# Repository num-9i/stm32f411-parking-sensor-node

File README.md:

# STM32F411RE Parking Sensor Node

STM32F411RE 기반으로 초음파 거리 측정, 주차 상태 판정, RGB LED 표시, Modbus RTU/RS485 통신을 구현한 주차 센서 노드 프로젝트입니다.

HC-SR04의 Echo pulse를 Timer Input Capture로 비동기 측정하고, 측정 결과에 hysteresis와 entry/exit delay를 적용해 `FREE / OCCUPIED / ERROR` 상태를 판정합니다.

센서 상태와 설정값은 Modbus Holding Register에 매핑했으며, `0x03 Read Holding Registers`와 `0x06 Write Single Register`를 통해 외부 Modbus Master에서 조회 및 변경할 수 있도록 구현했습니다.

현재 브레드보드 환경에서 펌웨어와 RS485 통신 검증을 완료했으며, NUCLEO-F411RE용 Carrier PCB도 Gerber/Drill 파일 생성 단계까지 완료했습니다. 실제 PCB 제작과 Bring-up은 다음 단계로 진행할 예정입니다.

## Project Status

- [x] Pin Map 정의
- [x] HC-SR04 거리 측정
- [x] TIM2 Input Capture / Interrupt 처리
- [x] 거리 측정 Timeout / Error Counter
- [x] FREE / OCCUPIED / ERROR 상태 판정
- [x] Hysteresis / Entry Delay / Exit Delay
- [x] RGB LED 상태 표시
- [x] Modbus RTU Function `0x03`
- [x] Modbus RTU Function `0x06`
- [x] Runtime Configuration
- [x] Modbus Exception Response
- [x] RS485 실통신 검증
- [x] Carrier PCB Schematic
- [x] Carrier PCB Layout / Routing
- [x] Carrier PCB ERC / DRC Verification
- [x] Gerber / Drill File Generation & Inspection
- [x] MAX3485용 PB5 DE/RE 제어 펌웨어 반영
- [ ] UART CLI
- [ ] PCB Fabrication
- [ ] PCB Bring-up / Hardware Verification

## System Overview

전체 데이터 흐름은 다음과 같습니다.

```text
HC-SR04
   │
   │ Echo Pulse
   ↓
TIM2 Input Capture
   │
   ↓
Distance Measurement
   │
   ↓
Parking State Logic
FREE / OCCUPIED / ERROR
   │
   ├──────────────→ RGB LED
   │
   ↓
Modbus Register Layer
   │
   ↓
Modbus RTU
   │
   ↓
USART1 / RS485
   │
   ↓
External Modbus Master
```

HC-SR04의 Echo pulse는 `TIM2_CH1 Input Capture`로 측정합니다.

측정된 거리 값은 주차 상태 판정 로직으로 전달되며, hysteresis와 entry/exit delay를 적용해 순간적인 거리 변화로 상태가 불필요하게 전환되는 것을 줄였습니다.

판정 결과와 센서 상태, 오류 카운터, 설정값은 Modbus Holding Register에 매핑해 외부 Master에서 확인할 수 있도록 구성했습니다.

## Hardware

### MCU / Development Board

- MCU: STM32F411RET6
- Board: NUCLEO-F411RE
- System Clock: 84 MHz

### Sensor / Indicator

- Distance Sensor: HC-SR04
- Status Indicator: Common Cathode RGB LED
- HC-SR04 Echo Interface: 1 kΩ / 2 kΩ Voltage Divider

### Communication

- Modbus UART: USART1
- Debug UART: USART2 / ST-LINK VCP
- Protocol: Modbus RTU
- Prototype RS485: Auto-direction TTL-to-RS485 Module
- Carrier PCB RS485: MAX3485
- PC Interface: USB-to-RS485 Adapter

상세 핀 구성은 아래 문서를 참고합니다.

- [Pin Map](docs/pin_map.md)

## HC-SR04 Distance Measurement

HC-SR04의 Trigger 신호를 출력한 뒤 Echo pulse의 High 구간을 측정해 거리를 계산합니다.

Echo 입력은 `PA0 / TIM2_CH1`에 연결하고, Timer를 1 MHz로 설정해 1 us 단위로 pulse width를 측정합니다.

```text
IDLE
  ↓
Trigger Pulse
  ↓
WAIT_RISING
  ↓
Rising Edge Capture
  ↓
WAIT_FALLING
  ↓
Falling Edge Capture
  ↓
Pulse Width Calculation
  ↓
DATA_READY
```

거리 계산에는 다음 관계를 사용합니다.

```text
Distance_mm = PulseWidth_us × 343 / 2000
```

센서 측정 범위는 약 `20 ~ 4000 mm`로 제한하며, 범위를 벗어난 pulse는 Invalid Pulse로 처리합니다.

정상적인 Echo 신호가 들어오지 않을 경우 무한 대기하지 않도록 Timeout을 적용했습니다.

구분하는 오류 항목은 다음과 같습니다.

- Rising Edge Timeout
- Falling Edge Timeout
- Invalid Pulse

각 오류는 별도의 Counter로 기록해 Modbus를 통해 확인할 수 있습니다.

## Parking State Logic

주차 상태는 다음 세 가지로 구분합니다.

| Value | State | Description |
|---:|---|---|
| `0` | FREE | 주차 공간이 비어 있는 상태 |
| `1` | OCCUPIED | 차량이 감지된 상태 |
| `2` | ERROR | 거리 측정이 일정 시간 이상 유효하지 않은 상태 |

기본 설정값은 다음과 같습니다.

```text
Occupied Threshold = 500 mm
Hysteresis         = 50 mm
Entry Delay        = 500 ms
Exit Delay         = 1000 ms
```

FREE 상태에서 거리가 `Occupied Threshold` 이하로 Entry Delay 동안 유지되면 OCCUPIED로 전환됩니다.

OCCUPIED 상태에서는 다음 기준을 사용합니다.

```text
Free Threshold =
    Occupied Threshold + Hysteresis
```

기본값 기준으로:

```text
Occupied Threshold = 500 mm
Free Threshold     = 550 mm
```

이므로 `500 mm < distance <= 550 mm` 구간에서는 현재 상태를 유지합니다.

따라서 임계값 부근에서 측정값이 흔들려도 상태가 즉시 반복 전환되지 않습니다.

거리 측정이 일정 시간 이상 유효하지 않을 경우 ERROR 상태로 전환합니다.

## RGB LED

주차 상태는 RGB LED로 표시합니다.

| Parking State | LED |
|---|---|
| FREE | Green |
| OCCUPIED | Red |
| ERROR | Blue |

GPIO 구성:

```text
PB12 → Red
PB13 → Green
PB14 → Blue
```

RGB LED는 Active High 방식으로 제어합니다.

## Modbus RTU / RS485

외부 장치에서 센서 상태와 설정값을 확인하거나 변경할 수 있도록 Modbus RTU Slave를 구현했습니다.

지원하는 Function Code는 다음과 같습니다.

- `0x03` Read Holding Registers
- `0x06` Write Single Register

통신 설정:

- Slave ID: `1`
- Baud Rate: `115200`
- Format: `8-N-1`
- Interface: USART1 / RS485

### Prototype RS485

브레드보드 프로토타입에서는 자동 방향 제어 TTL-to-RS485 모듈을 사용했습니다.

```text
PA9  / USART1_TX  → RS485 Module RXD
PA10 / USART1_RX  ← RS485 Module TXD
```

모듈 내부에서 송수신 방향을 자동으로 전환하므로 별도의 DE/RE GPIO가 필요하지 않습니다.

### Carrier PCB RS485

Carrier PCB에서는 `MAX3485`를 사용합니다.

```text
PA9  / USART1_TX  → MAX3485 DI
PA10 / USART1_RX  ← MAX3485 RO
PB5               → MAX3485 DE + /RE
```

`DE`와 `/RE`는 하나의 GPIO로 묶어 다음과 같이 제어합니다.

```text
PB5 LOW  → Receive Mode
PB5 HIGH → Transmit Mode
```

Modbus 응답을 송신하기 직전에 PB5를 HIGH로 설정하고, `HAL_UART_Transmit()` 완료 후 LOW로 복귀시켜 다시 Receive Mode로 전환합니다.

PCB에는 PB5에 10 kΩ Pull-down 저항을 적용해 MCU Reset 중에도 기본적으로 Driver가 비활성화되고 Receiver가 활성화되도록 구성했습니다.

브레드보드의 자동 방향 제어 모듈에는 PB5가 연결되지 않으므로, 해당 제어 코드를 추가한 뒤에도 기존 Prototype의 FC03 / FC06 통신이 정상적으로 동작하는 것을 확인했습니다.

## Holding Register Map

| Address | Name | Access |
|---|---|---|
| `0x0000` | Distance_mm | R |
| `0x0001` | Parking_State | R |
| `0x0002` | Status_Flags | R |
| `0x0003` | Total_Error_Count | R |
| `0x0004` | Rising_Timeout_Count | R |
| `0x0005` | Falling_Timeout_Count | R |
| `0x0006` | Invalid_Pulse_Count | R |
| `0x0007` | Occupied_Threshold_mm | R/W |
| `0x0008` | Hysteresis_mm | R/W |
| `0x0009` | Entry_Delay_ms | R/W |
| `0x000A` | Exit_Delay_ms | R/W |

상세한 Register Map과 설정값 검증 규칙은 아래 문서에 정리했습니다.

- [Modbus Register Map](docs/register_map.md)

## Runtime Configuration

`0x0007`~`0x000A` Register는 Modbus `0x06 Write Single Register`를 통해 실행 중에 변경할 수 있습니다.

예를 들어 Occupied Threshold의 기본값은 500 mm입니다.

```text
Register: 0x0007

500 mm
0x01F4

      ↓ FC06

300 mm
0x012C
```

설정값을 변경하면 주차 상태 판정 로직에서 즉시 새로운 값을 사용합니다.

현재 설정값은 RAM에만 저장되므로 Reset 또는 전원 재인가 후에는 기본값으로 돌아갑니다.

## Modbus Exception Handling

지원하지 않는 요청이나 잘못된 설정값에는 Modbus Exception Response를 반환합니다.

| Exception | Description |
|---|---|
| `0x01` | Illegal Function |
| `0x02` | Illegal Data Address |
| `0x03` | Illegal Data Value |

예를 들어 읽기 전용 Register인 `0x0000`에 `0x06` Write 요청을 보내면 `0x02 Illegal Data Address`를 반환합니다.

허용 범위를 벗어난 Occupied Threshold를 설정하면 `0x03 Illegal Data Value`를 반환합니다.

## Verification

### FC03 — Holding Register Read

Modbus Client에서 `0x0000`~`0x000A` Register를 한 번에 읽어 거리, 주차 상태, 오류 카운터, 설정값을 확인했습니다.

### Request / Response Frame

UART Debug 출력을 통해 실제 Modbus RTU Request와 Response 데이터를 확인했습니다.

### FC06 — Runtime Threshold Change

Occupied Threshold를 `500 mm`에서 `300 mm`로 변경한 뒤 Write 결과와 실제 주차 상태 전환 기준 변경을 확인했습니다.

### Exception — Illegal Data Address

읽기 전용 Register에 Write 요청을 전송해 `0x02 Illegal Data Address` 응답을 확인했습니다.

### Exception — Illegal Data Value

허용 범위를 벗어난 설정값을 전송해 `0x03 Illegal Data Value` 응답을 확인했습니다.

## Carrier PCB Design

브레드보드 프로토타입을 실제 조립 가능한 구조로 확장하기 위해 NUCLEO-F411RE용 Carrier PCB를 KiCad로 설계했습니다.

Carrier PCB에는 다음 회로를 포함합니다.

- NUCLEO-F411RE Interface
- HC-SR04 Connector
- HC-SR04 Echo Voltage Divider
- RGB Status LED
- MAX3485 RS485 Transceiver
- MAX3485 100 nF Decoupling Capacitor
- PB5 DE/RE Pull-down
- RS485 A / B / GND Terminal Block
- Selectable 120 Ω RS485 Termination

RS485 종단저항은 Solder Jumper를 사용해 필요할 때만 활성화할 수 있도록 구성했습니다.

```text
RS485_A ── 120 Ω ── JP1 ── RS485_B
```

### PCB 3D Overview

### RS485 / Sensor Section

PCB는 2-Layer로 구성했으며, B.Cu에 GND Copper Zone을 적용했습니다. ERC와 DRC는 모두 Error / Warning 0건을 확인했습니다.

구매한 Common Cathode RGB LED의 `B-G-K-R` Pin Order에 맞춰 전용 Footprint를 추가하고, D1의 Drill Diameter를 `0.8 mm`로 조정해 Annular Ring 규칙을 만족시켰습니다.

이후 Gerber와 PTH / NPTH Drill File을 생성하고 KiCad Gerber Viewer에서 Edge.Cuts, Copper, Solder Mask, Silkscreen, Drill Layer를 확인했습니다.

KiCad 프로젝트와 제조용 출력 파일은 다음 경로에 포함되어 있습니다.

```text
hardware/
└─ parking_sensor_node/
   ├─ parking_sensor_node.kicad_pro
   ├─ parking_sensor_node.kicad_sch
   ├─ parking_sensor_node.kicad_pcb
   ├─ fp-lib-table
   ├─ footprints/
   │  └─ ParkingSensor.pretty/
   │     └─ LED_D5.0mm-4_RGB_BGKR.kicad_mod
   └─ gerber/
      ├─ *.gbr
      ├─ *-PTH.drl
      └─ *-NPTH.drl
```

## Software Structure

주요 모듈은 다음과 같이 분리했습니다.

```text
Core/
├─ Inc/
│  ├─ hcsr04.h
│  ├─ parking_logic.h
│  ├─ rgb_led.h
│  ├─ app_config.h
│  ├─ modbus_crc.h
│  ├─ modbus_registers.h
│  └─ modbus_rtu.h
│
└─ Src/
   ├─ hcsr04.c
   ├─ parking_logic.c
   ├─ rgb_led.c
   ├─ app_config.c
   ├─ modbus_crc.c
   ├─ modbus_registers.c
   └─ modbus_rtu.c
```

각 모듈의 역할을 분리해 센서 측정, 상태 판정, 설정값 관리, Register Mapping, Modbus Frame 처리가 서로 직접 의존하지 않도록 구성했습니다.

## Current Limitations

현재 구현은 프로젝트 범위에 맞춰 다음과 같이 제한되어 있습니다.

- Modbus Function `0x03`, `0x06`만 지원
- UART RX는 현재 지원하는 8-byte Request Frame을 기준으로 처리
- Generic Modbus RTU Frame Gap Detection 미구현
- 통신 중 Partial Frame이 남은 상태에서 Master가 재연결될 경우 Frame 정렬이 깨질 수 있음
- 설정값은 RAM에만 저장
- UART CLI 미구현
- Carrier PCB 실물 제작 및 Bring-up 미완료
- MAX3485 기반 수동 DE/RE 제어는 펌웨어에 반영했으나 실제 Carrier PCB에서의 Hardware Verification은 아직 진행 전

현재 브레드보드 환경에서는 센서 측정, 상태 판정, RGB 표시, Modbus FC03 / FC06, Exception Response 및 RS485 실통신까지 검증했습니다.

## Next Step

다음 단계에서는 구매한 부품이 도착한 뒤 실제 부품과 Footprint를 대조하고 Carrier PCB 제작 및 Bring-up을 진행합니다.

제작 전 실물 기준으로 다음 항목을 확인할 예정입니다.

- MAX3485 SOIC-8 Package
- 3-pin RS485 Terminal Block의 5.08 mm Pitch / 방향
- RGB LED의 실제 Pin Order / Lead Pitch
- HC-SR04 Connector 및 기구 간섭

PCB 제작 후에는 다음 항목을 검증할 예정입니다.

```text
Power / Ground
    ↓
HC-SR04 Measurement
    ↓
RGB State Output
    ↓
MAX3485 DE/RE Control
    ↓
Modbus FC03 / FC06
    ↓
Exception Response
    ↓
Long-term Communication Test
```

PCB 제작 후에는 브레드보드에서 검증한 기능을 Carrier PCB에서도 동일한 순서로 Bring-up할 예정입니다.

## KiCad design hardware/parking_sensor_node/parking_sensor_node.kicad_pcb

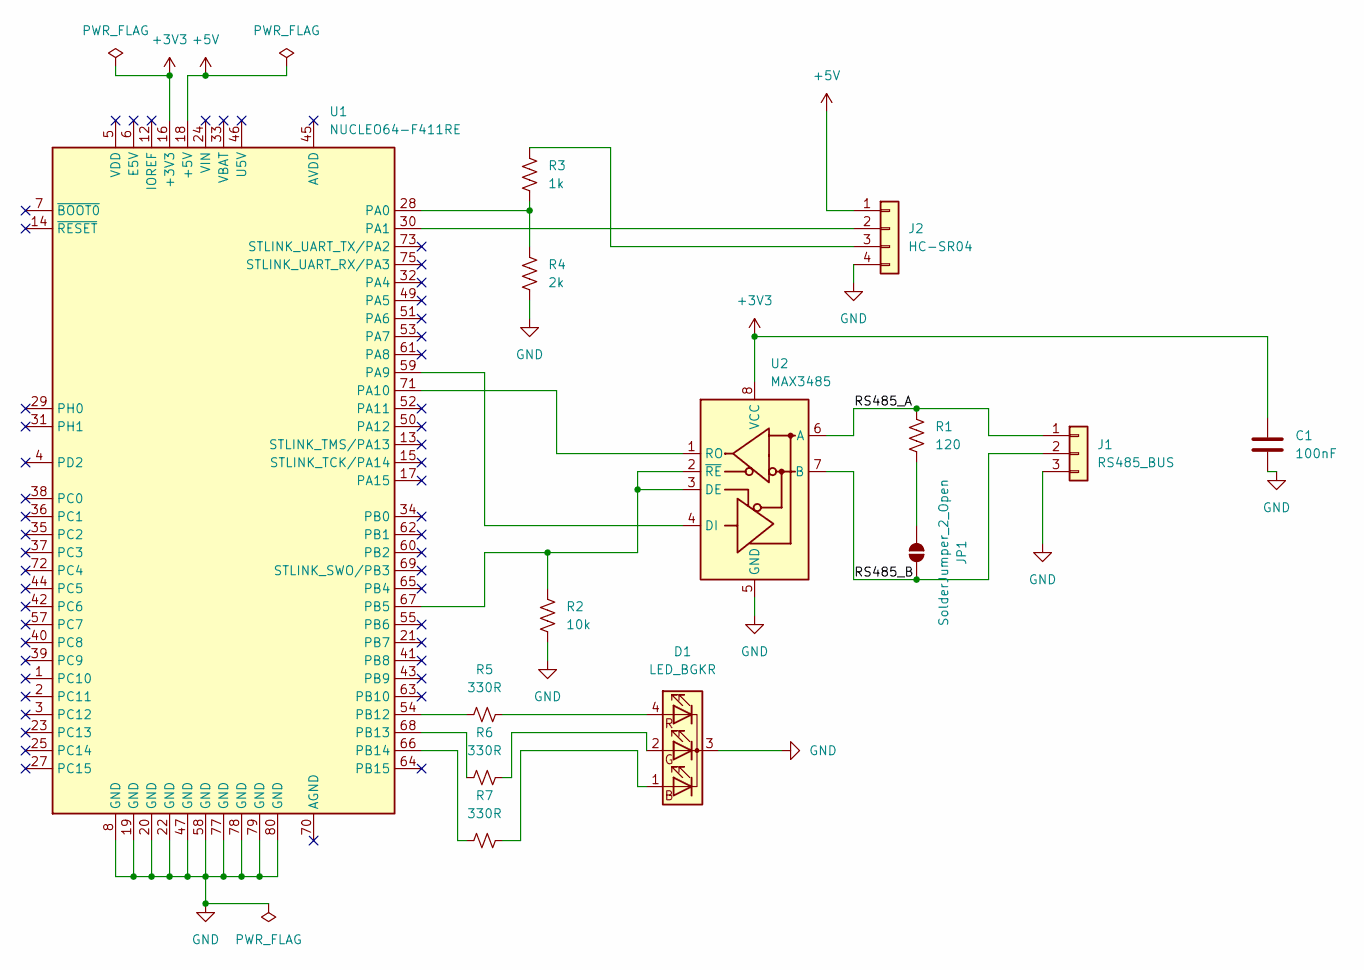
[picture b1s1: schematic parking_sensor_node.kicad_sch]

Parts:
C1: 100nF; C_0805_2012Metric
D1: LED_BGKR; LED_D5.0mm-4_RGB_BGKR
J1: RS485_BUS; TerminalBlock_Phoenix_MKDS-3-3-5.08_1x03_P5.08mm_Horizontal
J2: HC-SR04; PinSocket_1x04_P2.54mm_Vertical
JP1: SolderJumper_2_Open; SolderJumper-2_P1.3mm_Open_Pad1.0x1.5mm
R1: 120; R_0805_2012Metric
R2: 10k; R_0805_2012Metric
R3: 1k; R_0805_2012Metric
R4: 2k; R_0805_2012Metric
R5, R6, R7: 330R; R_0805_2012Metric
U1: NUCLEO64-F411RE; ST_Morpho_Connector_64_STLink
U2: MAX3485; SOIC-8_3.9x4.9mm_P1.27mm

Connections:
+3V3: C1.1, U1.16 (+3V3), U2.8 (VCC)
+5V: J2.1, U1.18 (+5V)
/RS485_A: J1.1, R1.1, U2.6 (A)
/RS485_B: J1.2, JP1.2 (B), U2.7 (B)
GND: C1.2, D1.3 (K), J1.3, J2.4, R2.2, R4.2, U1.8 (GND), U1.19 (GND), U1.20 (GND), U1.22 (GND), U1.47 (GND), U1.58 (GND), U1.77 (GND), U1.78 (GND), U1.79 (GND), U1.80 (GND), U2.5 (GND)
unnamed: D1.1 (BA), R7.2
unnamed: D1.2 (GA), R6.2
unnamed: D1.4 (RA), R5.2
unnamed: J2.2, U1.30 (PA1)
unnamed: J2.3, R3.1
unnamed: JP1.1 (A), R1.2
unnamed: R3.2, R4.1, U1.28 (PA0)
unnamed: U1.59 (PA9), U2.4 (DI)
unnamed: U1.71 (PA10), U2.1 (RO)
unnamed: R2.1, U1.67 (PB5), U2.2 (~RE), U2.3 (DE)
unnamed: R5.1, U1.54 (PB12)
unnamed: R6.1, U1.68 (PB13)
unnamed: R7.1, U1.66 (PB14)

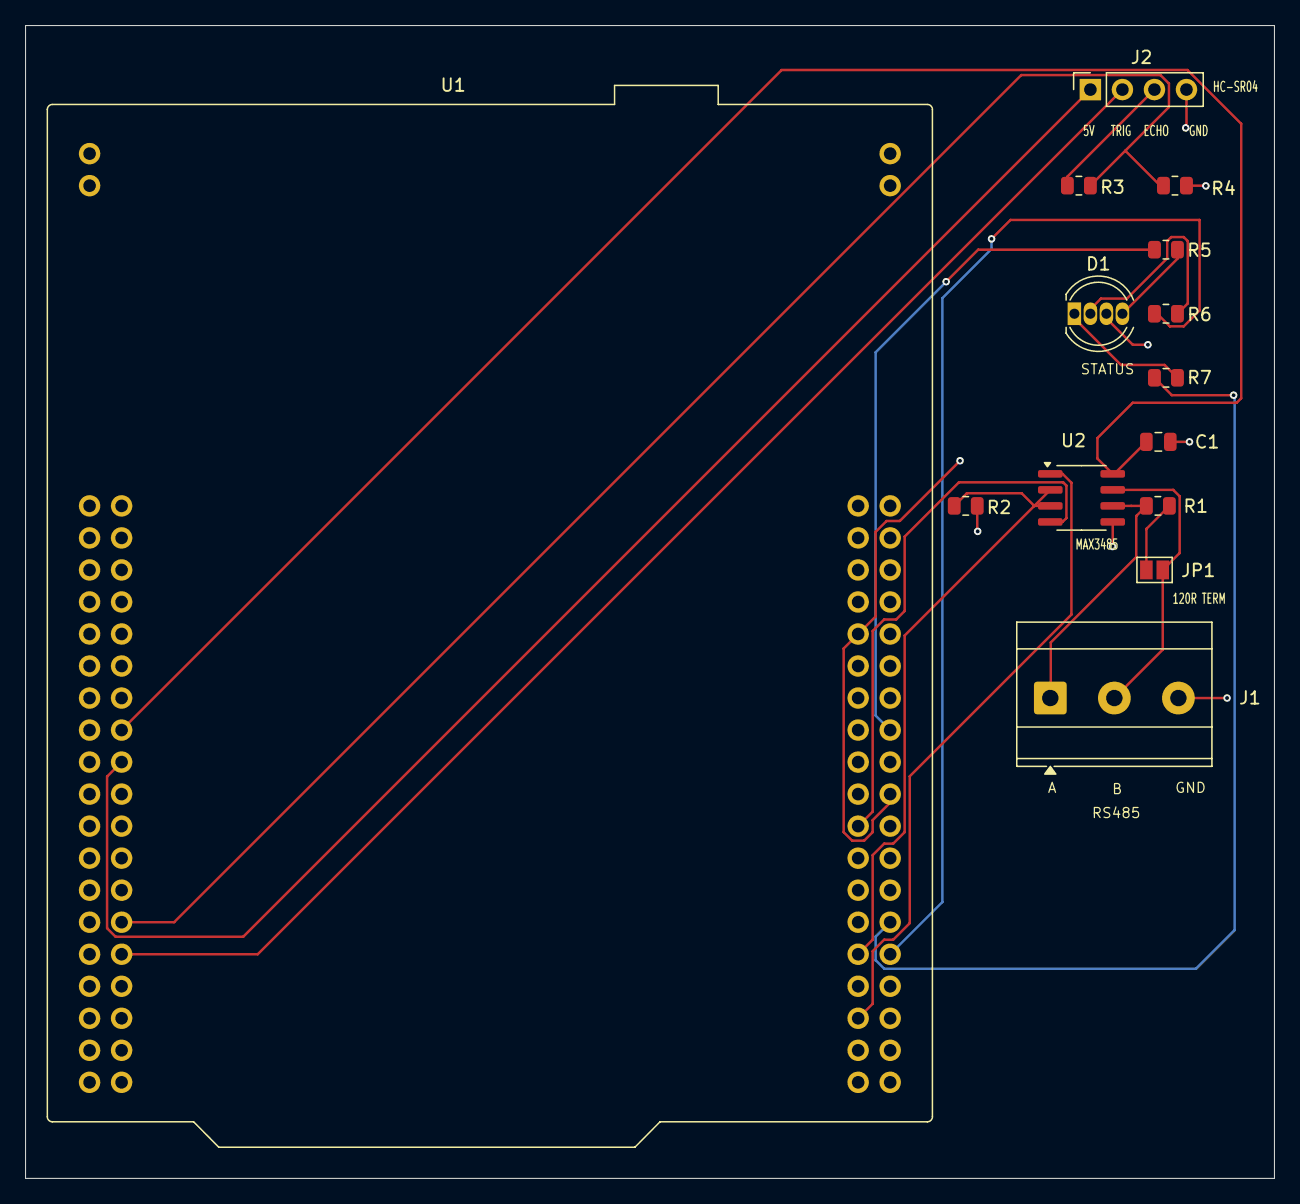
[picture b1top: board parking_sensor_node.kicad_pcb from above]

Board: 2 copper layers, 99.1 x 91.4 mm, 14 parts (0 on the bottom side), 18 nets.
